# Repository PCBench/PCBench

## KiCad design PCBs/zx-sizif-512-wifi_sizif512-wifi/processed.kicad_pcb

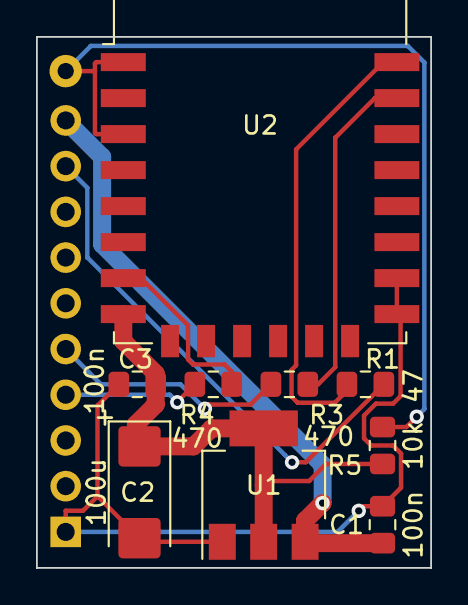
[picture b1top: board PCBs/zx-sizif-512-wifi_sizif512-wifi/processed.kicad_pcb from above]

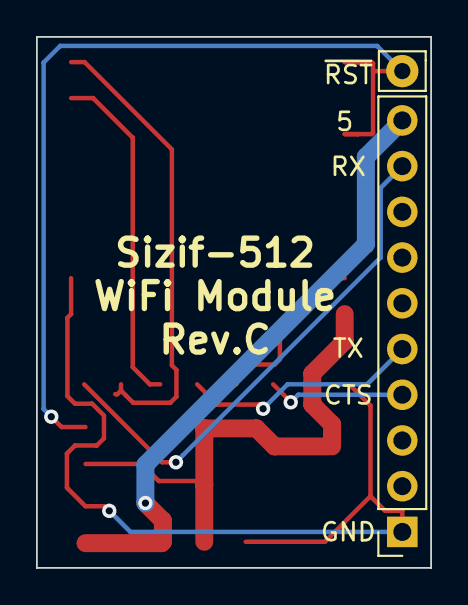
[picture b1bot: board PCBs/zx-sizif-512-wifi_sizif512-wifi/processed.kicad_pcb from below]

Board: 2 copper layers, 21.9 x 29.5 mm, 11 parts (2 on the bottom side), 10 nets.

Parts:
C1, C3: 100n; C_0805_2012Metric_Pad1.15x1.40mm_HandSolder
C2: 100u; CP_EIA-6032-15_Kemet-U_Pad2.25x2.35mm_HandSolder
J1: Conn_01x10; PinSocket_1x10_P2.54mm_Vertical
R1: 47; C_0805_2012Metric_Pad1.15x1.40mm_HandSolder
R3, R4: 470; C_0805_2012Metric_Pad1.15x1.40mm_HandSolder
R5: 10k; C_0805_2012Metric_Pad1.15x1.40mm_HandSolder
TP1: TestPoint; Pin_D0.9mm_L10.0mm_W2.4mm_FlatFork
U1: AMS1117-3.3; SOT-223-3_TabPin2
U2: ESP-12E

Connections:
+3V3: C2.1, C3.1, R5.2, U1.2, U2.8
+5V: C1.1, J1.10, U1.3
CTS: J1.4, R4.2
GND: C1.2, C2.2, C3.2, J1.1, U1.1, U2.15, U2.16
unnamed: R1.1, U2.22
unnamed: R3.1, U2.21
unnamed: R4.1, U2.7
unnamed: R5.1, TP1.1, U2.1, U2.3
RX: J1.9, R1.2
TX: J1.5, R3.2

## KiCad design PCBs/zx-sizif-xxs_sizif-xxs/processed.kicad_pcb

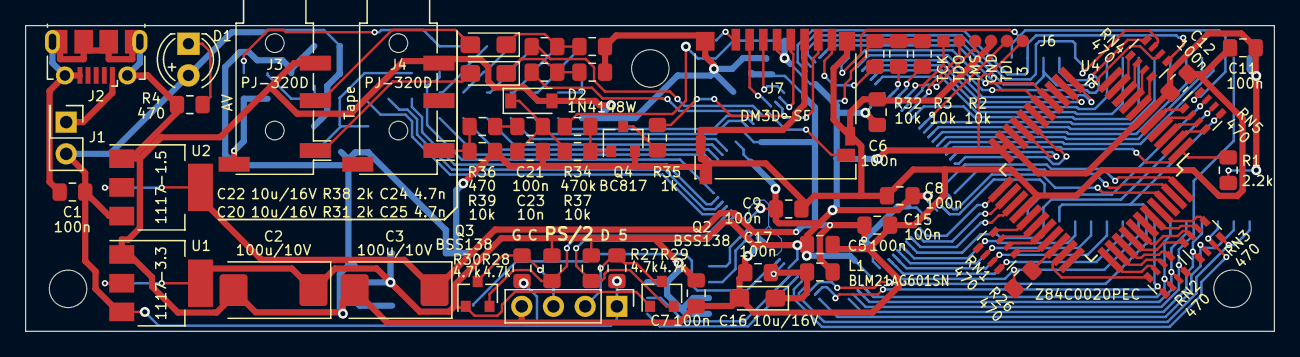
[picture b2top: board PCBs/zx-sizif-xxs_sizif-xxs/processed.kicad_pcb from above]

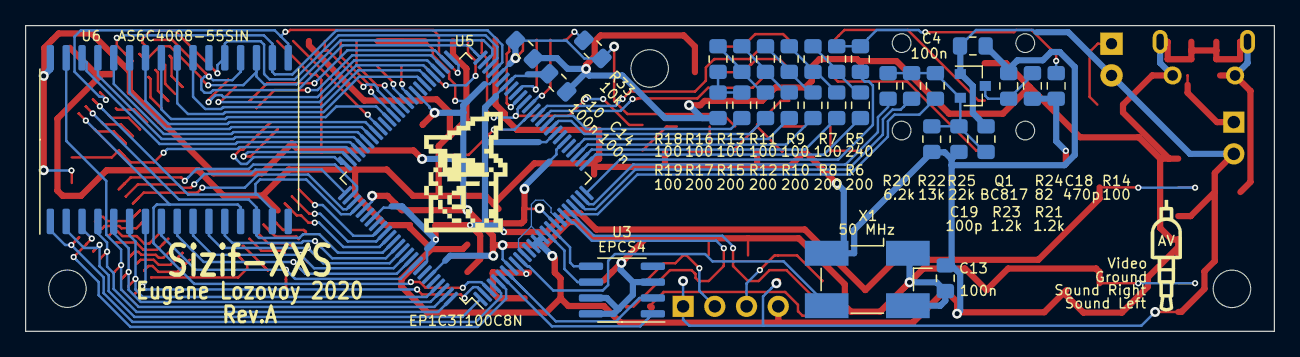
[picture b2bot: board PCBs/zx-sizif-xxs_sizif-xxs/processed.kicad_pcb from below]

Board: 2 copper layers, 100.0 x 24.5 mm, 95 parts (35 on the bottom side), 123 nets.

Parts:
C1, C4, C5, C6, C7, C8, C9, C10, C11, C12, C13, C14, C15, C17, C21: 100n; C_0805_2012Metric_Pad1.15x1.40mm_HandSolder
C2, C3: 100u/10V; CP_EIA-7343-31_Kemet-D_Pad2.25x2.55mm_HandSolder
C16, C20, C22: 10u/16V; CP_EIA-3216-18_Kemet-A_Pad1.58x1.35mm_HandSolder
C18: 470p; C_0805_2012Metric_Pad1.15x1.40mm_HandSolder
C19: 100p; C_0805_2012Metric_Pad1.15x1.40mm_HandSolder
C23: 10n; C_0805_2012Metric_Pad1.15x1.40mm_HandSolder
C24, C25: 4.7n; C_0805_2012Metric_Pad1.15x1.40mm_HandSolder
D1: LED; LED_D4.0mm
D2: 1N4148W; D_SOD-123
H1, H2, H3: MountingHole; MountingHole_3mm
J1: Pin header 1x2 Pitch=2.54mm; PinHeader_2x01_P2.54mm_Vertical
J2: USB_B_Micro; USB_Micro-B_Molex-105017-0001
J3, J4: PJ-320D; Jack_3.5mm_PJ320D_Horizontal
J5: Pin header 1x4 Pitch=2.54mm; PinHeader_1x04_P2.54mm_Vertical
J6: Solder points; PinPoints_1x06_P1.27mm
J7: DM3D-SF; microSD_HC_Hirose_DM3D-SF
L1: BLM21AG601SN; L_0805_2012Metric_Pad1.15x1.40mm_HandSolder
LOGO1: graphic; black-mage3
LOGO2: Jack35; jack35_4pin
Q1, Q4: BC817; SOT-23
Q2, Q3: BSS138; SOT-23
R1: 2.2k; R_0805_2012Metric_Pad1.15x1.40mm_HandSolder
R2, R3, R32, R33, R37, R39: 10k; R_0805_2012Metric_Pad1.15x1.40mm_HandSolder
R4, R26, R36: 470; R_0805_2012Metric_Pad1.15x1.40mm_HandSolder
R5: 240; R_0805_2012Metric_Pad1.15x1.40mm_HandSolder
R6, R8, R10, R12, R15, R17: 200; R_0805_2012Metric_Pad1.15x1.40mm_HandSolder
R7, R9, R11, R13, R14, R16, R18, R19: 100; R_0805_2012Metric_Pad1.15x1.40mm_HandSolder
R20: 6.2k; R_0805_2012Metric_Pad1.15x1.40mm_HandSolder
R21, R23: 1.2k; R_0805_2012Metric_Pad1.15x1.40mm_HandSolder
R22: 13k; R_0805_2012Metric_Pad1.15x1.40mm_HandSolder
R24: 82; R_0805_2012Metric_Pad1.15x1.40mm_HandSolder
R25: 22k; R_0805_2012Metric_Pad1.15x1.40mm_HandSolder
R27, R28, R29, R30: 4.7k; R_0805_2012Metric_Pad1.15x1.40mm_HandSolder
R31, R38: 2k; R_0805_2012Metric_Pad1.15x1.40mm_HandSolder
R34: 470k; R_0805_2012Metric_Pad1.15x1.40mm_HandSolder
R35: 1k; R_0805_2012Metric_Pad1.15x1.40mm_HandSolder
RN1, RN2, RN3, RN4, RN5: 470; R_Array_Convex_4x0603
U1: 1117-3.3; SOT-223-3_TabPin2
U2: 1117-1.5; SOT-223-3_TabPin2
U3: EPCS4; SOIC-8_3.9x4.9mm_P1.27mm
U4: Z84C0020PEC; TQFP-44_14x14mm_P0.8mm
U5: EP1C3T100C8N; TQFP-100_14x14mm_P0.5mm
U6: AS6C4008-55SIN; SSOP-32_11.305x20.495mm_P1.27mm
X1: 50 MHz; Oscillator_SMD_EuroQuartz_XO91-4Pin_7.0x5.0mm_HandSoldering

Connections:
1V5_PLL: C16.1, C17.2, L1.2, U5.9
+1V5: C3.1, C14.1, C15.2, L1.1, U2.2, U5.33, U5.44, U5.82, U5.93
+3V3: C2.1, C5.2, C6.1, C7.1, C8.1, C9.1, C10.1, C11.1, C12.1, C13.1, J6.6, J7.4, Q2.1, Q3.1, R1.2, R2.1, R3.1, R27.2, R28.2, R32.1, R33.1, R34.2, U1.2, U3.3, U3.7, U3.8, U4.6, U4.21, U4.22, U5.8, U5.18, U5.31, U5.46, U5.59, U5.80, U5.95, U6.32, X1.1, X1.4
+5V: C1.2, C4.2, D1.2, J1.2, J5.1, Q1.1, R21.1, R29.2, R30.2, U1.3, U2.3
/A0: RN1.8, U4.27
/A1: RN1.7, U4.28
/A2: RN1.6, U4.29
/A3: RN1.5, U4.30
/A4: R26.2, U4.31
/A5: RN2.8, U4.32
/A6: RN2.7, U4.34
/A7: RN2.6, U4.35
/A8: RN2.5, U4.36
/A9: RN3.8, U4.37
/A10: RN3.7, U4.38
/A11: RN3.6, U4.40
/A12: RN3.5, U4.41
/A13: U4.42, U5.78
/A14: U4.43, U5.76
/A15: U4.44, U5.77
/CLK: U5.10, X1.3
/CLKCPU: R1.1, U4.1, U5.73
/Chroma0: R25.1, U5.22
/Chroma1: R22.1, U5.23
/Chroma2: R20.1, U5.24
/Csync: R5.1, U5.25
/D0: RN4.6, U4.9
/D1: RN4.5, U4.10
/D2: RN4.8, U4.7
/D3: RN5.7, U4.3
/D4: RN5.8, U4.2
/D5: RN5.6, U4.4
/D6: RN5.5, U4.5
/D7: RN4.7, U4.8
/EPCS_ASD: U3.5, U5.17
/EPCS_DATA: U3.2, U5.7
/EPCS_DCLK: U3.6, U5.16
/PS2_CLK: Q3.2, R28.1, U5.21
/PS2_DAT: Q2.2, R27.1, U5.20
/SD_CD: J7.9, U5.38
/SD_CS: J7.2, U5.39
/SD_MISO\TAPE: J7.7, R35.2, U5.40
/SD_MOSI: J7.3, U5.42
/SD_SCK: J7.5, U5.41
/SND_DAC_L: R31.1, U5.36
/SND_DAC_R: R38.1, U5.37
/SND_L: C20.2, J3.T
/SND_R: C22.2, J3.R1
/TAPE_IN: J4.T, R36.1, R39.1
/TCK: J6.1, U5.62
/TDI: J6.5, U5.67
/TDO: J6.2, U5.64
/TMS: J6.3, U5.63
/V0: R17.1, U5.35
/V1: R15.1, U5.34
/V2: R12.1, U5.29
/V3: R10.1, U5.28
/V4: R8.1, U5.27
/V5: R6.1, U5.26
/VA0: RN1.1, U5.88, U6.12
/VA1: RN1.2, U5.89, U6.11
/VA2: RN1.3, U5.90, U6.10
/VA3: RN1.4, U5.91, U6.9
/VA4: R26.1, U5.92, U6.8
/VA5: RN2.1, U5.2, U6.7
/VA6: RN2.2, U5.97, U6.6
/VA7: RN2.3, U5.98, U6.5
/VA8: RN2.4, U5.99, U6.31
/VA9: RN3.1, U5.100, U6.4
/VA10: RN3.2, U5.1, U6.2
/VA11: RN3.3, U5.5, U6.3
/VA12: RN3.4, U5.4, U6.1
/VA13: U5.70, U6.28
/VA14: U5.56, U6.23
/VA15: U5.69, U6.27
/VA16: U5.65, U6.25
/VA17: U5.72, U6.30
/VA18: U5.68, U6.26
/VD0: RN4.3, U5.48, U6.21
/VD1: RN4.4, U5.50, U6.20
/VD2: RN4.1, U5.47, U6.18
/VD3: RN5.2, U5.87, U6.14
/VD4: RN5.1, U5.3, U6.13
/VD5: RN5.3, U5.79, U6.15
/VD6: RN5.4, U5.51, U6.17
/VD7: RN4.2, U5.49, U6.19
/Video: C18.2, J3.S, R14.1
/~EPCS_CS: U3.1, U5.6
/~INT: U4.12, U5.54
/~IORQ: U4.16, U5.53
/~M1: U4.24, U5.85
/~MREQ: U4.15, U5.52
/~NMI: U4.13, U5.55
/~RD: U4.18, U5.75
/~RFSH: U4.25, U5.86
/~RSTCPU: U4.23, U5.84
/~VRD: U5.57, U6.24
/~VWR: U5.71, U6.29
/~WR: U4.19, U5.74
GND: C1.1, C2.2, C3.2, C4.1, C5.1, C6.2, C7.2, C8.2, C9.2, C10.2, C11.2, C12.2, C13.2, C14.2, C15.1, C16.2, C17.1, C19.2, C23.2, C24.2, C25.2, D2.2, J2.5, J2.6, J3.R2, J4.R2, J5.4, J6.4, J7.6, J7.10, J7.11, Q4.2, R4.2, R19.1, R23.1, R24.1, R39.2, U1.1, U2.1, U4.26, U5.11, U5.13, U5.14, U5.15, U5.19, X1.2
unnamed: C18.1, Q1.3, R24.2
unnamed: C19.1, Q1.2, R20.2, R21.2, R22.2, R23.2, R25.2
unnamed: C20.1, C25.1, R31.2
unnamed: C21.1, C23.1, D2.1, R37.1
unnamed: C21.2, R36.2
unnamed: C22.1, C24.1, R38.2
unnamed: D1.1, R4.1
unnamed: J1.1, J2.1
unnamed: J5.2, Q2.3, R29.1
unnamed: J5.3, Q3.3, R30.1
unnamed: J7.1, R33.2
unnamed: J7.8, R32.2
unnamed: Q4.1, R34.1, R37.2
unnamed: Q4.3, R35.1
unnamed: R2.2, U5.61
unnamed: R3.2, U5.60
unnamed: R6.2, R7.1, R9.2
unnamed: R10.2, R11.1, R13.2
unnamed: R8.2, R9.1, R11.2
unnamed: R12.2, R13.1, R16.2
unnamed: R5.2, R7.2, R14.2
unnamed: R15.2, R16.1, R18.2
unnamed: R17.2, R18.1, R19.2

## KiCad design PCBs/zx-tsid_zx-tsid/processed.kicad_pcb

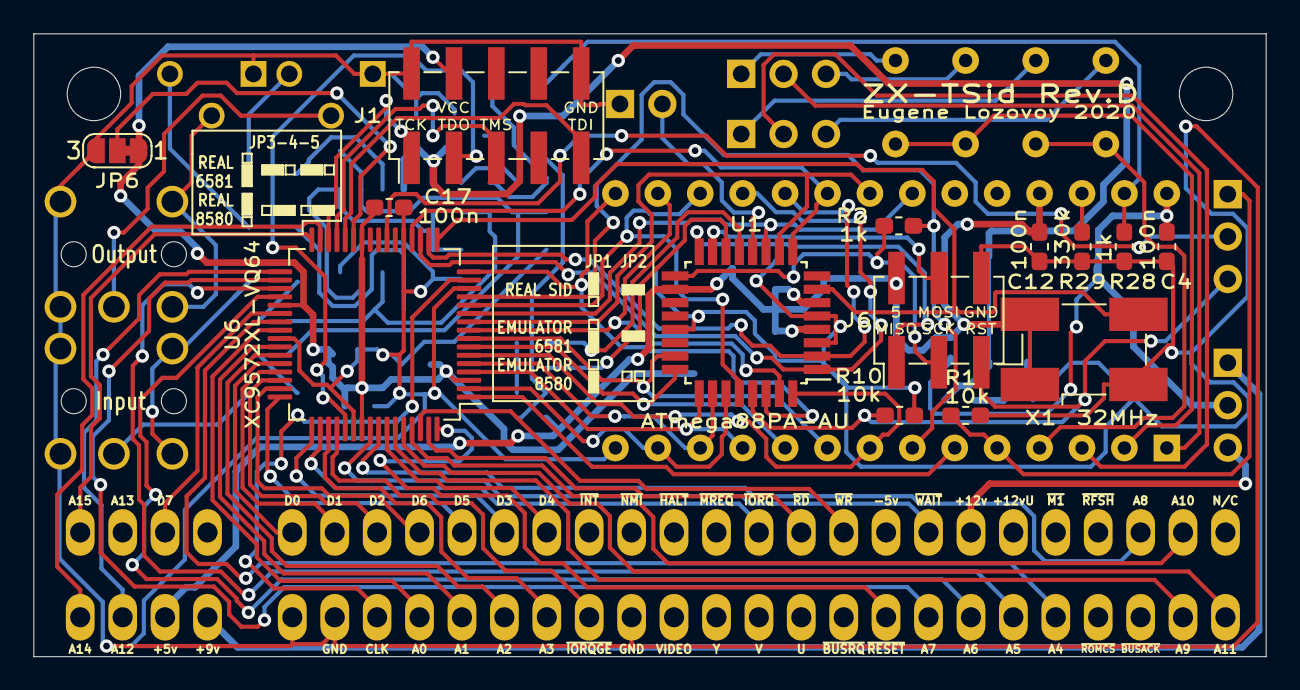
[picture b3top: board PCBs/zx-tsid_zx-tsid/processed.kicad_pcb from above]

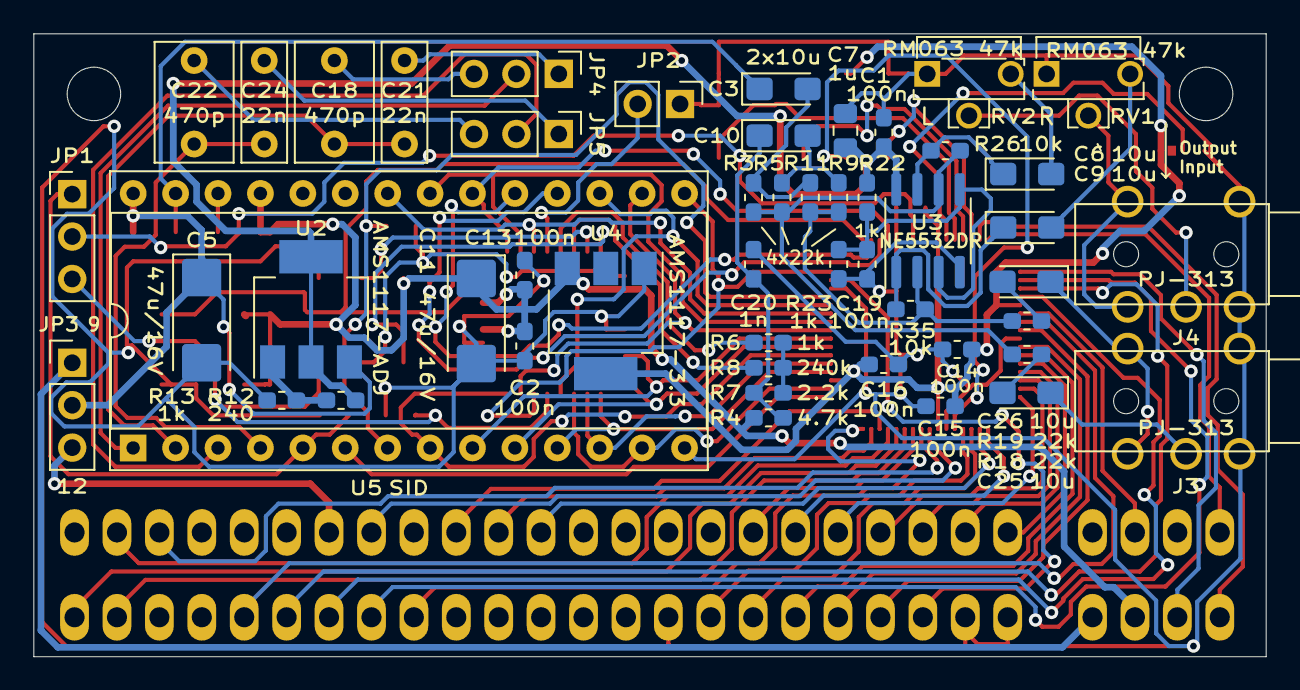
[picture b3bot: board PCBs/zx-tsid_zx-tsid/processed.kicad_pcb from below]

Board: 2 copper layers, 73.8 x 37.3 mm, 67 parts (52 on the bottom side), 96 nets.

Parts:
C1, C2, C4, C12, C13, C14, C15, C16, C17, C19: 100n; C_0603_1608Metric_Pad1.05x0.95mm_HandSolder
C3, C6, C9, C10, C25, C26: 10u; CP_EIA-3216-18_Kemet-A_Pad1.58x1.35mm_HandSolder
C5, C11: 47u/16V; CP_EIA-6032-28_Kemet-C_Pad2.25x2.35mm_HandSolder
C7: 1u; C_0805_2012Metric_Pad1.15x1.40mm_HandSolder
C18, C22: 470p; C_Rect_L7.0mm_W4.5mm_P5.00mm
C20: 1n; C_0603_1608Metric_Pad1.05x0.95mm_HandSolder
C21, C24: 22n; C_Rect_L7.0mm_W2.5mm_P5.00mm
H1, H2: MountingHole; MountingHole_3.2mm_M3
J1: Conn_02x05_Odd_Even; PinHeader_2x05_P2.54mm_Vertical_SMD
J2: zx_edge; Spectrum_Edge_Connector
J3, J4: PJ-313
J6: Conn_02x03_Odd_Even; PinHeader_2x03_P2.54mm_Vertical_SMD
JP1, JP3, JP4, JP5: Jumper_3_Open; PinHeader_1x03_P2.54mm_Vertical
JP2: Jumper; PinHeader_1x02_P2.54mm_Vertical
JP6: Jumper_3_Bridged12; SolderJumper-3_P1.3mm_Bridged12_RoundedPad1.0x1.5mm_NumberL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
R1, R10, R26, R35: 10k; R_0603_1608Metric_Pad1.05x0.95mm_HandSolder
R2, R6, R13, R22, R23, R28: 1k; R_0603_1608Metric_Pad1.05x0.95mm_HandSolder
R3, R5, R9, R11, R18, R19: 22k; R_0603_1608Metric_Pad1.05x0.95mm_HandSolder
R4: 4.7k; R_0603_1608Metric_Pad1.05x0.95mm_HandSolder
R7: 2.2k; R_0603_1608Metric_Pad1.05x0.95mm_HandSolder
R8: 240k; R_0603_1608Metric_Pad1.05x0.95mm_HandSolder
R12: 240; R_0603_1608Metric_Pad1.05x0.95mm_HandSolder
R29: 330k; R_0603_1608Metric_Pad1.05x0.95mm_HandSolder
RV1, RV2: RM063 47k; Potentiometer_Runtron_RM-063_Horizontal
U1: ATmega88PA-AU; TQFP-32_7x7mm_P0.8mm
U2: AMS1117-ADJ; SOT-223-3_TabPin2
U3: NE5532DR; SOIC-8_3.9x4.9mm_P1.27mm
U4: AMS1117-3.3; SOT-223-3_TabPin2
U5: 8580; DIP-28_W15.24mm_Socket
U6: XC9572XL-VQ64; TQFP-64_10x10mm_P0.5mm
X1: 32MHz; Oscillator_SMD_EuroQuartz_XO91-4Pin_7.0x5.0mm_HandSoldering

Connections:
+3V3: C14.1, C15.1, C16.1, C17.1, J1.4, JP6.1, U4.2, U6.3, U6.26, U6.37, U6.55
+5V: C2.1, C11.1, C12.1, C13.1, J2.A3, J6.2, R4.2, U1.4, U1.6, U1.18, U4.3, U5.25, X1.1, X1.4
+6V: C1.2, C7.2, R12.2, R22.2, U2.2, U3.8
+9V: J2.A4, JP3.1
+12V: J2.B22, JP3.3
/L: J4.T, RV1.2
/R: J4.R, RV2.2
A0: J2.A9, U6.40
A1: J2.A10, U6.42
A2: J2.A11, U6.43
A3: J2.A12, U6.51
A4: J2.A24, U6.39
A5: J2.A23, U6.35
A6: J2.A22, U6.36
A7: J2.A21, U6.34
A8: J2.B26, U6.57
A9: J2.A27, U6.59
A10: J2.B27, U6.61
A11: J2.A28, U6.60
A12: J2.A2, U6.33
A14: J2.A1, U6.31
A15: J2.B1, U6.32
CLK32: U1.7, U6.17, X1.3
D0: J2.B6, U6.44
D1: J2.B7, U6.45
D2: J2.B8, U6.46
D3: J2.B11, U6.49
D4: J2.B12, U6.58
D5: J2.B10, U6.48
D6: J2.B9, U6.47
D7: J2.B3, U6.38
GND: C1.1, C2.2, C4.1, C5.2, C7.1, C11.2, C12.2, C13.2, C14.2, C15.2, C16.2, C17.2, C19.1, C20.2, J1.2, J1.10, J2.A6, J2.A7, J2.A14, J3.S, J4.S, J6.6, JP2.1, JP6.3, R1.2, R10.2, R13.1, R23.1, R28.2, R29.2, RV1.1, RV2.1, U1.3, U1.5, U1.21, U3.4, U4.1, U5.14, U6.14, U6.21, U6.41, U6.54, X1.2
MISO: J6.1, U1.16
MOSI: J6.4, U1.15
unnamed: C3.1, R28.1, U5.27
unnamed: C3.2, R3.2, R11.2
unnamed: C6.1, R26.1, U3.7
unnamed: C6.2, RV2.3
unnamed: C9.1, R35.1, U3.1
unnamed: C9.2, RV1.3
unnamed: C10.1, C20.1, R4.1, R7.1
unnamed: C10.2, R5.2, R9.2
unnamed: C18.1, C21.2, U5.2
unnamed: C18.2, JP4.3
unnamed: C19.2, R22.1, R23.2, U3.3, U3.5
unnamed: C21.1, JP4.1
unnamed: C22.1, C24.1, U5.4
unnamed: C22.2, JP5.3
unnamed: C24.2, JP5.1
unnamed: C25.1, J3.R
unnamed: C25.2, R18.2
unnamed: C26.1, J3.T
unnamed: C26.2, R19.2
unnamed: JP2.2, U1.12
unnamed: JP4.2, U5.1
unnamed: JP5.2, U5.3
unnamed: JP6.2, U6.27
unnamed: R6.1, U1.13
unnamed: R6.2, R7.2, R8.1
unnamed: R8.2, U1.14
unnamed: R9.1, R11.1, R19.1, R35.2, U3.2
unnamed: R12.1, R13.2, U2.1
unnamed: R3.1, R5.1, R18.1, R26.2, U3.6
unnamed: R29.1, U5.26
SCK: J6.3, R2.2, U1.17
SID_A0: U1.23, U5.9, U6.8
SID_A1: U1.24, U5.10, U6.7
SID_A2: U1.25, U5.11, U6.4
SID_A3: U1.26, U5.12, U6.5
SID_A4: U1.27, U5.13, U6.2
SID_CLK: U5.6, U6.1
SID_D0: U1.30, U5.15, U6.16
SID_D1: U1.31, U5.16, U6.9
SID_D2: U1.28, U5.17, U6.12
SID_D3: U1.1, U5.18, U6.19
SID_D4: U1.2, U5.19, U6.18
SID_D5: U1.9, U5.20, U6.20
SID_D6: U1.10, U5.21, U6.10
SID_D7: U1.11, U5.22, U6.11
TCK: J1.1, U6.30
TDI: J1.9, U6.28
TDO: J1.3, U6.53
TMS: J1.5, U6.29
VDDA: C4.2, C5.1, JP3.2, U2.3, U5.28
~AVR_RST: J6.5, JP1.3, R10.1, U1.29
~CLKCPU: J2.A8, U6.15
~IORQ: J2.B17, U6.50
~IORQGE: J2.A13, U6.52
~RD: J2.B18, U6.63
~REAL_RST: JP1.1, R1.1, U5.5
~RST: J2.A20, U6.64
~SID_CS: U1.32, U5.8, U6.6
~SID_RST: JP1.2, U6.23
~SID_WR: R2.1, U5.7, U6.13
~WAIT: J2.B21, U6.56
~WR: J2.B19, U6.62

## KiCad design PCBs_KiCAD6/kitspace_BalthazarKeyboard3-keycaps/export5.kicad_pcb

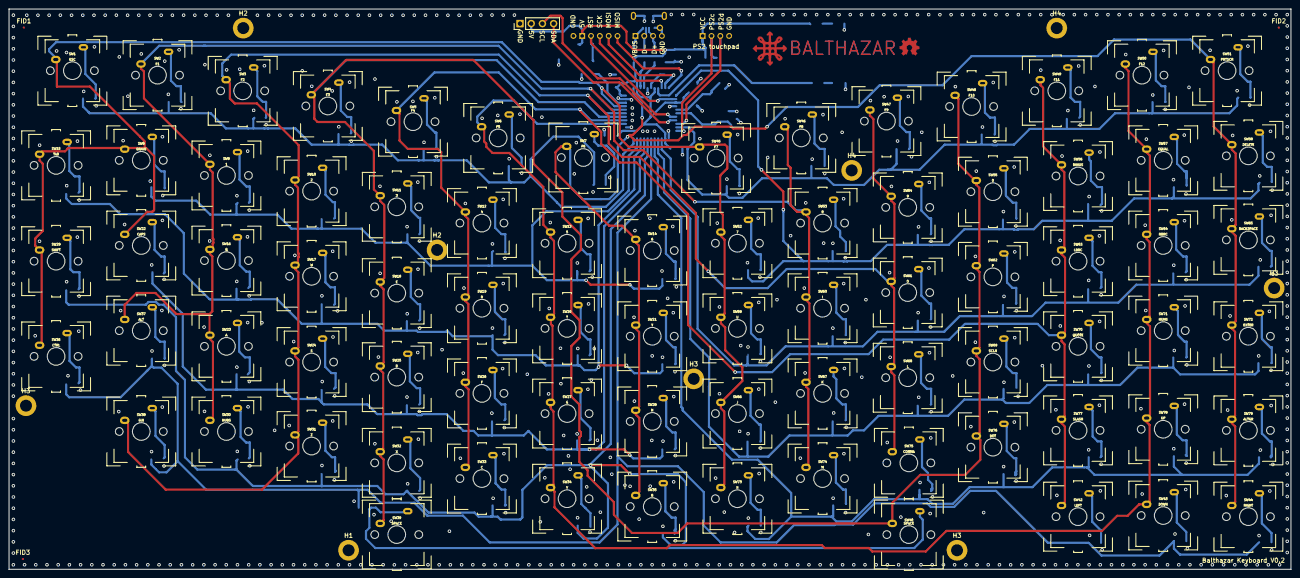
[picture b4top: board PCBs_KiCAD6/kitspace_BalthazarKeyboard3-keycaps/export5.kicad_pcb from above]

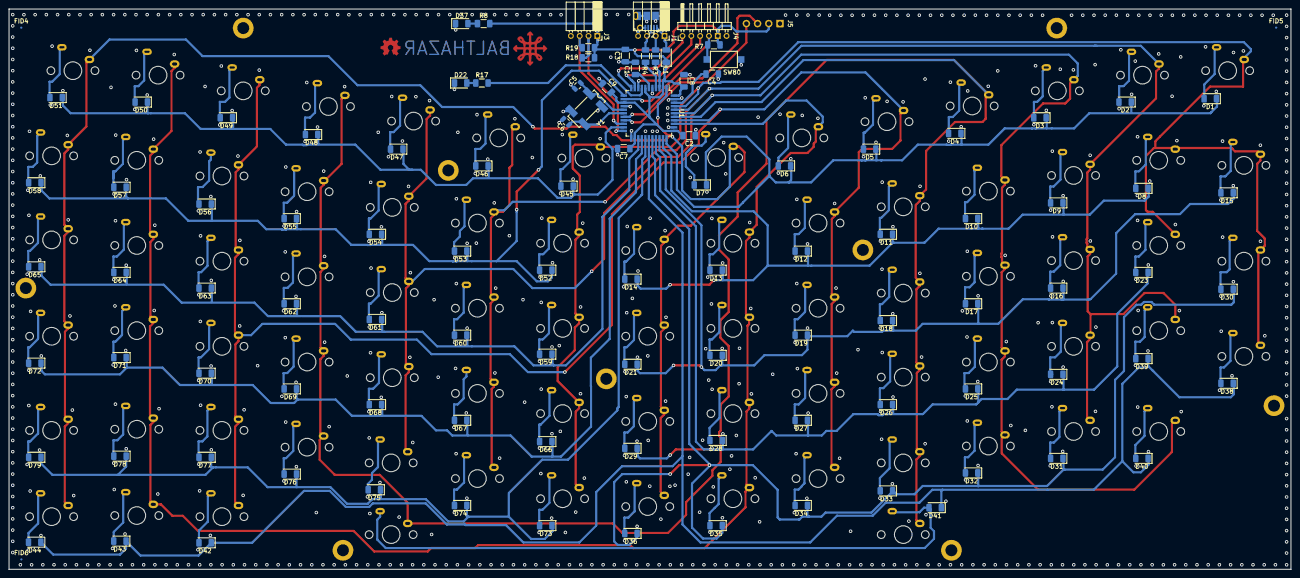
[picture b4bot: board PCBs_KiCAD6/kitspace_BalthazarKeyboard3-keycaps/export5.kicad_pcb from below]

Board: 2 copper layers, 290.6 x 127.0 mm, 197 parts (106 on the bottom side), 117 nets.

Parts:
C1: 1uF; C_1206_3216Metric
C2: 10uF; C_1206_3216Metric
C3, C4, C7, C8, C9: 0.1uF; C_1206_3216Metric
C5, C6: 22pF; C_0805_2012Metric
D1, D2, D3, D4, D5, D6, D7, D8, D9, D10, D11, D12, D13, D14, D15, D16, D17, D18, D19, D20, D21, D23, D24, D25, D26, D27, D28, D29, D30, D31, D32, D33, D34, D35, D36, D38, D39, D40, D41, D42, D43, D44, D45, D46, D47, D48, D49, D50, D51, D52, D53, D54, D55, D56, D57, D58, D59, D60, D61, D62, D63, D64, D65, D66, D67, D68, D69, D70, D71, D72, D73, D74, D75, D76, D77, D78, D79: D; D_1206_3216Metric
D22, D37: LED_Small; LED_1206_3216Metric
FID1, FID2, FID3, FID4, FID5, FID6: Fiducial; Fiducial_0.5mm_Mask1mm
H1, H2, H2#2, H3, H3#2, H3#3, H3#4, H4, H4#2: MountingHole_Pad; MountingHole_2.7mm_M2.5_DIN965_Pad
J1: USB; PinSocket_1x04_P2.00mm_Horizontal
J2: USB_B_Micro; USB_Micro-B_Molex-Balthazar
J3: PS2 touchpad; PinSocket_1x04_P2.00mm_Horizontal
J4: ISP; PinHeader_1x06_P2.00mm_Horizontal
J5: I2C; PinHeader_1x04_P2.54mm_Vertical
L1: L_Core_Ferrite_Small; D_1206_3216Metric
R3, R4: 22; R_1206_3216Metric
R7, R18, R19: 10K; R_1206_3216Metric
R8, R17: 200; R_1206_3216Metric
SW1: ESC; CherryMX_RGB_SpeedSilver
SW2: F1; CherryMX_RGB_SpeedSilver
SW3: F2; CherryMX_RGB_SpeedSilver
SW4: F3; CherryMX_RGB_SpeedSilver
SW5: F4; CherryMX_RGB_SpeedSilver
SW6: F5; CherryMX_RGB_SpeedSilver
SW7: F6; CherryMX_RGB_SpeedSilver
SW8: GRAVE; CherryMX_RGB_SpeedSilver
SW9: 1; CherryMX_RGB_SpeedSilver
SW10: 2; CherryMX_RGB_SpeedSilver
SW11: 3; CherryMX_RGB_SpeedSilver
SW12: 4; CherryMX_RGB_SpeedSilver
SW13: 5; CherryMX_RGB_SpeedSilver
SW14: 6; CherryMX_RGB_SpeedSilver
SW15: TAB; CherryMX_RGB_SpeedSilver
SW16: Q; CherryMX_RGB_SpeedSilver
SW17: W; CherryMX_RGB_SpeedSilver
SW18: E; CherryMX_RGB_SpeedSilver
SW19: R; CherryMX_RGB_SpeedSilver
SW20: T; CherryMX_RGB_SpeedSilver
SW21: Y; CherryMX_RGB_SpeedSilver
SW22: CAPS; CherryMX_RGB_SpeedSilver
SW23: A; CherryMX_RGB_SpeedSilver
SW24: S; CherryMX_RGB_SpeedSilver
SW25: D; CherryMX_RGB_SpeedSilver
SW26: F; CherryMX_RGB_SpeedSilver
SW27: G; CherryMX_RGB_SpeedSilver
SW28: H; CherryMX_RGB_SpeedSilver
SW29: SHIFT; CherryMX_RGB_SpeedSilver
SW30: NUBS; CherryMX_RGB_SpeedSilver
SW31: Z; CherryMX_RGB_SpeedSilver
SW32: X; CherryMX_RGB_SpeedSilver
SW33: C; CherryMX_RGB_SpeedSilver
SW34: V; CherryMX_RGB_SpeedSilver
SW35: B; CherryMX_RGB_SpeedSilver
SW36: CTRL; CherryMX_RGB_SpeedSilver
SW37: ALT; CherryMX_RGB_SpeedSilver
SW38: GUI; CherryMX_RGB_SpeedSilver
SW39, SW40: SPACE; CherryMX_RGB_SpeedSilver
SW42: LEFT; CherryMX_RGB_SpeedSilver
SW43: DOWN; CherryMX_RGB_SpeedSilver
SW44: RIGHT; CherryMX_RGB_SpeedSilver
SW45: F7; CherryMX_RGB_SpeedSilver
SW46: F8; CherryMX_RGB_SpeedSilver
SW47: F9; CherryMX_RGB_SpeedSilver
SW48: F10; CherryMX_RGB_SpeedSilver
SW49: F11; CherryMX_RGB_SpeedSilver
SW50: F12; CherryMX_RGB_SpeedSilver
SW51: PRTSCR; CherryMX_RGB_SpeedSilver
SW52: 7; CherryMX_RGB_SpeedSilver
SW53: 8; CherryMX_RGB_SpeedSilver
SW54: 9; CherryMX_RGB_SpeedSilver
SW55: 0; CherryMX_RGB_SpeedSilver
SW56: MINUS; CherryMX_RGB_SpeedSilver
SW57: EQUAL; CherryMX_RGB_SpeedSilver
SW58: DELETE; CherryMX_RGB_SpeedSilver
SW59: U; CherryMX_RGB_SpeedSilver
SW60: I; CherryMX_RGB_SpeedSilver
SW61: O; CherryMX_RGB_SpeedSilver
SW62: P; CherryMX_RGB_SpeedSilver
SW63: LBRC; CherryMX_RGB_SpeedSilver
SW64: RBRC; CherryMX_RGB_SpeedSilver
SW65: BACKSPACE; CherryMX_RGB_SpeedSilver
SW66: J; CherryMX_RGB_SpeedSilver
SW67: K; CherryMX_RGB_SpeedSilver
SW68: L; CherryMX_RGB_SpeedSilver
SW69: SCLN; CherryMX_RGB_SpeedSilver
SW70: QUOTE; CherryMX_RGB_SpeedSilver
SW71: NUHS; CherryMX_RGB_SpeedSilver
SW72: ENTER; CherryMX_RGB_SpeedSilver
SW73: N; CherryMX_RGB_SpeedSilver
SW74: M; CherryMX_RGB_SpeedSilver
SW75: COMMA; CherryMX_RGB_SpeedSilver
SW76: DOT; CherryMX_RGB_SpeedSilver
SW77: SLASH; CherryMX_RGB_SpeedSilver
SW78: UP; CherryMX_RGB_SpeedSilver
SW79: ALTGR; CherryMX_RGB_SpeedSilver
SW80: SW_Push; SW_SPST_CK_RS282G05A3
U1: ATmega32U4_Balthazar; TQFP-44_10x10mm_P0.8mm
Y1: Crystal_16M; Crystal_SMD_SeikoEpson_MC306-4Pin_8.0x3.2mm_HandSoldering

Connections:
GND: C1.2, C2.1, C3.1, C4.2, C5.2, C6.2, C7.1, C8.1, C9.1, D22.1, D37.1, H1.1, H2.1, H2#2.1, H3.1, H3#2.1, H3#3.1, H3#4.1, H4.1, H4#2.1, J1.4, J2.5, J2.6, J3.4, J4.6, J5.1, SW80.1, U1.5, U1.15, U1.23, U1.35, U1.43, Y1.2, Y1.4
unnamed: C1.1, U1.6
unnamed: C4.1, U1.42
unnamed: C5.1, U1.16, Y1.1
unnamed: C6.1, U1.17, Y1.3
unnamed: D1.2, SW1.2
unnamed: D2.2, SW2.2
unnamed: D3.2, SW3.2
unnamed: D4.2, SW4.2
unnamed: D5.2, SW5.2
unnamed: D6.2, SW6.2
unnamed: D7.2, SW7.2
unnamed: D8.2, SW8.2
unnamed: D9.2, SW9.2
unnamed: D10.2, SW10.2
unnamed: D11.2, SW11.2
unnamed: D12.2, SW12.2
unnamed: D13.2, SW13.2
unnamed: D14.2, SW14.2
unnamed: D15.2, SW15.2
unnamed: D16.2, SW16.2
unnamed: D17.2, SW17.2
unnamed: D18.2, SW18.2
unnamed: D19.2, SW19.2
unnamed: D20.2, SW20.2
unnamed: D21.2, SW21.2
unnamed: D22.2, R17.1
unnamed: D23.2, SW22.2
unnamed: D24.2, SW23.2
unnamed: D25.2, SW24.2
unnamed: D26.2, SW25.2
unnamed: D27.2, SW26.2
unnamed: D28.2, SW27.2
unnamed: D29.2, SW28.2
unnamed: D30.2, SW29.2
unnamed: D31.2, SW30.2
unnamed: D32.2, SW31.2
unnamed: D33.2, SW32.2
unnamed: D34.2, SW33.2
unnamed: D35.2, SW34.2
unnamed: D36.2, SW35.2
unnamed: D37.2, R8.1
unnamed: D38.2, SW36.2
unnamed: D39.2, SW37.2
unnamed: D40.2, SW38.2
unnamed: D41.2, SW39.2, SW40.2
unnamed: D42.2, SW42.2
unnamed: D43.2, SW43.2
unnamed: D44.2, SW44.2
unnamed: D45.2, SW45.2
unnamed: D46.2, SW46.2
unnamed: D47.2, SW47.2
unnamed: D48.2, SW48.2
unnamed: D49.2, SW49.2
unnamed: D50.2, SW50.2
unnamed: D51.2, SW51.2
unnamed: D52.2, SW52.2
unnamed: D53.2, SW53.2
unnamed: D54.2, SW54.2
unnamed: D55.2, SW55.2
unnamed: D56.2, SW56.2
unnamed: D57.2, SW57.2
unnamed: D58.2, SW58.2
unnamed: D59.2, SW59.2
unnamed: D60.2, SW60.2
unnamed: D61.2, SW61.2
unnamed: D62.2, SW62.2
unnamed: D63.2, SW63.2
unnamed: D64.2, SW64.2
unnamed: D65.2, SW65.2
unnamed: D66.2, SW66.2
unnamed: D67.2, SW67.2
unnamed: D68.2, SW68.2
unnamed: D69.2, SW69.2
unnamed: D70.2, SW70.2
unnamed: D71.2, SW71.2
unnamed: D72.2, SW72.2
unnamed: D73.2, SW73.2
unnamed: D74.2, SW74.2
unnamed: D75.2, SW75.2
unnamed: D76.2, SW76.2
unnamed: D77.2, SW77.2
unnamed: D78.2, SW78.2
unnamed: D79.2, SW79.2
unnamed: J1.1, J2.1, L1.2
unnamed: J1.2, J2.2, R3.1
unnamed: J1.3, J2.3, R4.1
unnamed: J4.1, U1.11
unnamed: J4.2, U1.10
unnamed: J4.3, U1.9
unnamed: J5.3, U1.18
unnamed: J5.4, U1.19
unnamed: R3.2, U1.3
unnamed: R4.2, U1.4
unnamed: R17.2, U1.8
PS2clock: J3.2, R18.2, U1.22
PS2data: J3.3, R19.2, U1.20
RST: J4.4, R7.2, SW80.2, U1.13
Vcc: C2.2, C3.2, C7.2, C8.2, C9.2, J3.1, J4.5, J5.2, L1.1, R7.1, R8.2, R18.1, R19.1, U1.2, U1.7, U1.14, U1.24, U1.34, U1.44
col1: D1.1, D2.1, D3.1, D4.1, D5.1, D6.1, D7.1, U1.33
col2: D8.1, D9.1, D10.1, D11.1, D12.1, D13.1, D14.1, U1.32
col3: D15.1, D16.1, D17.1, D18.1, D19.1, D20.1, D21.1, U1.31
col4: D23.1, D24.1, D25.1, D26.1, D27.1, D28.1, D29.1, U1.30
col5: D30.1, D31.1, D32.1, D33.1, D34.1, D35.1, D36.1, U1.29
col6: D38.1, D39.1, D40.1, D41.1, D42.1, D43.1, D44.1, U1.28
col7: D73.1, D74.1, D75.1, D76.1, D77.1, D78.1, D79.1, U1.27
col8: D66.1, D67.1, D68.1, D69.1, D70.1, D71.1, D72.1, U1.26
col9: D59.1, D60.1, D61.1, D62.1, D63.1, D64.1, D65.1, U1.25
col10: D52.1, D53.1, D54.1, D55.1, D56.1, D57.1, D58.1, U1.12
col11: D45.1, D46.1, D47.1, D48.1, D49.1, D50.1, D51.1, U1.21
row1: SW1.1, SW8.1, SW15.1, SW22.1, SW29.1, SW36.1, SW45.1, SW52.1, SW59.1, SW66.1, SW73.1, U1.41
row2: SW2.1, SW9.1, SW16.1, SW23.1, SW30.1, SW37.1, SW46.1, SW53.1, SW60.1, SW67.1, SW74.1, U1.40
row3: SW3.1, SW10.1, SW17.1, SW24.1, SW31.1, SW38.1, SW47.1, SW54.1, SW61.1, SW68.1, SW75.1, U1.39
row4: SW4.1, SW11.1, SW18.1, SW25.1, SW32.1, SW39.1, SW40.1, SW48.1, SW55.1, SW62.1, SW69.1, SW76.1, U1.38
row5: SW5.1, SW12.1, SW19.1, SW26.1, SW33.1, SW42.1, SW49.1, SW56.1, SW63.1, SW70.1, SW77.1, U1.37
row6: SW6.1, SW13.1, SW20.1, SW27.1, SW34.1, SW43.1, SW50.1, SW57.1, SW64.1, SW71.1, SW78.1, U1.36
row7: SW7.1, SW14.1, SW21.1, SW28.1, SW35.1, SW44.1, SW51.1, SW58.1, SW65.1, SW72.1, SW79.1, U1.1

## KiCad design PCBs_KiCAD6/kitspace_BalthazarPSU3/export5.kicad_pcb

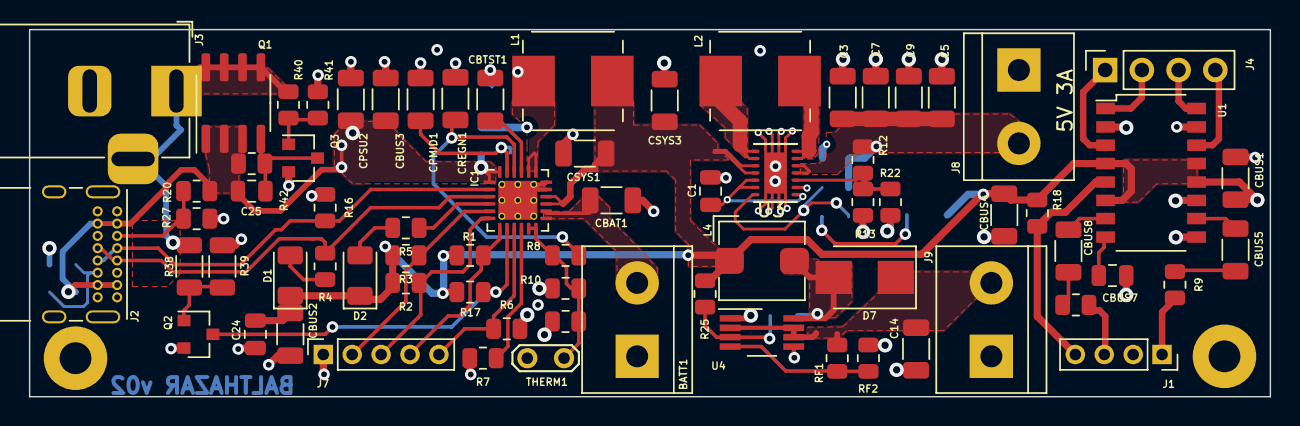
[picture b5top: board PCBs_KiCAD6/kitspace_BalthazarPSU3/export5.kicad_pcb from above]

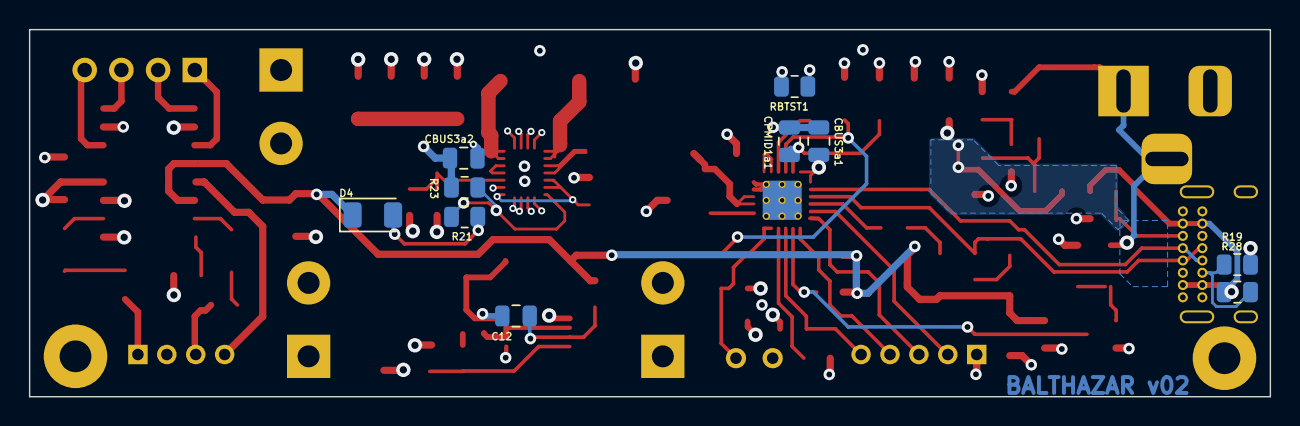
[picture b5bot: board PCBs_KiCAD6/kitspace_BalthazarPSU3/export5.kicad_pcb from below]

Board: 2 copper layers, 85.9 x 25.4 mm, 84 parts (10 on the bottom side), 50 nets.

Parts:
BATT1: 1s LiPo; TerminalBlock_bornier-2_P5.08mm
C1, C24: 0.1uF; C_0805_2012Metric
C3, C5, C7, C9, C14: 22uF; C_1206_3216Metric
C12: 4.7pF; C_0805_2012Metric
C25: 1nF; C_0805_2012Metric
CBAT1: 10uF; C_1206_3216Metric
CBTST1: 1uF; C_1206_3216Metric
CBUS1, CBUS4: 10uF; C_1206_3216Metric
CBUS2, CBUS3, CBUS5, CBUS8: 1uF; C_1206_3216Metric
CBUS3a1, CBUS3a2, CBUS7: 0.1uF; C_0805_2012Metric
CPMID1: 10uF; C_1206_3216Metric
CPMID1a1: 0.1uF; C_0805_2012Metric
CPSU2: 1uF; C_1206_3216Metric
CREGN1: 1uF; C_1206_3216Metric
CSYS1, CSYS3: 10uF; C_1206_3216Metric
D1, D2, D4: Led; LED_1206_3216Metric
D7: B320; D_SMB
H3: hole; MountingHole_2.2mm_M2_Pad
H4: MountingHole_Pad; MountingHole_2.2mm_M2_Pad
IC1: BQ24193; QFN-24-1EP_4x4mm_P0.5mm_EP2.7x2.7mm_ThermalVias
J1: AudioIN; PinSocket_1x04_P2.00mm_Vertical
J2: USB_C_Receptacle_USB2.0; USB_C_Receptacle_GCT_USB4085
J3: 5-15V / 3-5A; BarrelJack_Horizontal
J4: AudioOUT; PinSocket_1x04_P2.54mm_Vertical
J7: uC host; PinSocket_1x05_P2.00mm_Vertical
J8: 5V 3A; TerminalBlock_bornier-2_P5.08mm
J9: 12V 2A; TerminalBlock_bornier-2_P5.08mm
L1: 2.2uH 4A; L_Bourns_SRP7028A_7.3x6.6mm
L2: 1.5uH 4A; L_Bourns_SRP7028A_7.3x6.6mm
L4: 4.7uH 2A; L_Bourns_SRP5030T
Q1: IRF7404; SOIC-8_3.9x4.9mm_P1.27mm
Q2, Q3: BSS138; SOT-23
R1, R2, R3, R6, R16, R17, R18, R42: 10K; R_0805_2012Metric
R4, R5, R8, R9, R11, R21: 2K2; R_0805_2012Metric
R7: 265; R_0805_2012Metric
R10: 6K8; R_0805_2012Metric
R12, R23: 1M; R_0805_2012Metric
R13: 180K; R_0805_2012Metric
R19, R27: 5K1; R_0805_2012Metric
R20, R28: 56K; R_0805_2012Metric
R22: 270K; R_0805_2012Metric
R25: 150K; R_0805_2012Metric
R38: 120K; R_1206_3216Metric
R39: 49K9; R_1206_3216Metric
R40: 262K; R_0805_2012Metric
R41: 100K; R_0805_2012Metric
RBTST1: R; R_0805_2012Metric
RF1: 820K; R_0805_2012Metric
RF2: 100K; R_0805_2012Metric
THERM1: thermistor; TestPoint_2Pads_Pitch2.54mm_Drill0.8mm
THERMISTOR(103-AT)1: 10K; R_0805_2012Metric
U1: PAM8403-SOP16; SOP-16_4.4x10.4mm_P1.27mm
U3: TPS63020; QFN14-3X4MM
U4: LM2623; VSSOP-8_3.0x3.0mm_P0.65mm

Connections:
5V: C3.1, C5.1, C7.1, C9.1, CBUS3a2.2, J8.2, R12.2, R23.2, U3.4, U3.5
12V: C14.1, D7.1, J9.2, RF1.2, U4.2, U4.6, U4.7
/CE: IC1.9, J7.5, R6.1
/D+: IC1.2, J2.A6, J2.B6, R16.2
/D-: IC1.3, J2.A7, J2.B7, R4.1
/INT: IC1.7, J7.4, R1.1
/OTG: IC1.8, Q2.3, R17.1
/SCL: IC1.5, J7.2, R3.1
/SDA: IC1.6, J7.3, R2.1
unnamed: BATT1.2, CBAT1.2, IC1.13, IC1.14
unnamed: CBTST1.1, RBTST1.1
unnamed: CBUS5.1, R9.1
unnamed: CBUS8.1, R11.1
unnamed: D1.2, R4.2
unnamed: D2.2, R5.2
unnamed: D4.2, R21.1
unnamed: C12.2, D7.2, L4.2, U4.8
unnamed: CBTST1.2, IC1.21
unnamed: IC1.10, R7.1
unnamed: CREGN1.2, IC1.22, R8.1
unnamed: IC1.4, R5.1
unnamed: IC1.19, IC1.20, L1.1, RBTST1.2
unnamed: IC1.11, IC1.12, R8.2, R10.1, THERM1.2, THERMISTOR(103-AT)1.2
unnamed: J1.1, R9.2
unnamed: J1.3, R11.2
unnamed: J1.4, R18.2, U1.5
unnamed: J2.A5, R20.1, R27.2
unnamed: J2.B5, R19.2, R28.1
unnamed: J4.1, U1.3
unnamed: J4.2, U1.1
unnamed: J4.3, U1.16
unnamed: J4.4, U1.14
unnamed: C25.1, Q1.4, Q3.3, R42.2
unnamed: Q2.1, R38.2, R39.1
unnamed: Q3.1, R40.2, R41.1
unnamed: CBUS8.2, U1.7
unnamed: CBUS5.2, U1.10
unnamed: CBUS7.2, U1.8
unnamed: C1.1, U3.1, U3.12, U3.13
unnamed: R12.1, R13.2, R22.2, U3.3
unnamed: L2.1, U3.8, U3.9
unnamed: L2.2, U3.6, U3.7
unnamed: R21.2, R23.1, U3.14
unnamed: RF1.1, RF2.2, U4.4
unnamed: C12.1, R25.1, U4.3
PGND: BATT1.1, C1.2, C3.2, C5.2, C7.2, C9.2, C14.2, C24.1, CBAT1.1, CBUS1.1, CBUS2.2, CBUS3.1, CBUS3a1.1, CBUS3a2.1, CBUS4.1, CBUS7.1, CPMID1.1, CPMID1a1.1, CPSU2.1, CREGN1.1, CSYS1.2, CSYS3.2, H3.1, H4.1, IC1.17, IC1.18, IC1.25, J1.2, J2.A1, J2.A12, J2.B1, J2.B12, J2.S1, J3.2, J7.1, J8.1, J9.1, Q2.2, Q3.2, R6.2, R7.2, R10.2, R13.1, R16.1, R19.1, R22.1, R27.1, R39.2, R41.2, RF2.1, THERM1.1, THERMISTOR(103-AT)1.1, U1.2, U1.9, U1.11, U1.15, U3.2, U3.15, U3.16, U3.17, U3.18, U3.19, U3.20, U3.21, U3.22, U3.23, U4.1, U4.5
POWERBANKOUT: CPMID1.2, CPMID1a1.2, IC1.23
VBUS: C25.2, CBUS3.2, CBUS3a1.2, CPSU2.2, IC1.1, IC1.24, J2.A4, J2.A9, J2.B4, J2.B9, Q1.1, Q1.2, Q1.3, R20.2, R28.2, R42.1
VPSU: J3.1, Q1.5, Q1.6, Q1.7, Q1.8, R38.1, R40.1
VSYS: C24.2, CBUS1.2, CBUS2.1, CBUS4.2, CSYS1.1, CSYS3.1, D1.1, D2.1, D4.1, IC1.15, IC1.16, L1.2, L4.1, R1.2, R2.2, R3.2, R17.2, R18.1, R25.2, U1.4, U1.6, U1.12, U1.13, U3.10, U3.11

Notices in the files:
PCBs_KiCAD6/kitspace_BalthazarPSU3/export5.kicad_pcb:
License: CERN-OHL-S
PCBs_KiCAD6/kitspace_OSO-BOOK-C1/export5.kicad_pcb:
CC-BY-SA 4.0
PCBs_KiCAD6/kitspace_Oak/export5.kicad_pcb:
License: CC-BY-SA 4.0 or TAPR
